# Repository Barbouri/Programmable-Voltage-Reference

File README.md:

# Programmable-Voltage-Reference
An adjustable 0.001 to 5.000 volt reference, adjustable in 1 mV steps with display
==============================

This repository contains the design files and write-up for a Programmable Voltage Reference.  The reference has a range of 1 mV to 5.000 volts in 1 mV steps. The accuracy is plus or minus 50 uV for any set value. The reference value is displayed on a 2 X 16 character OLED display and can be set manually using the rotary encoder or remotely over the TTL serial to isolated USB 2.0 port.

The software folder contains an Arduino / Teensyduino sketch that is the source code for the voltage reference firmware.

Visit https://www.barbouri.com/2022/03/29/updating-the-programmable-voltage-reference-project/ for a more detailed explanation of the project design.

You can order this PCB directly from OSH Park.  Click on the following link.  
  * Programmable Voltage Reference V3.14- https://oshpark.com/shared_projects/pFu2IAUW

See the Bill of Materials (BOM) file in the repo Hardware folder for a parts list.  

## Status  
  * Version 3.14 PCB has been tested to be functional.
  * Version 3.15 PCB is untested with changes to silkscreen values and circuit trace widths.

## File Formats  

Hardware design files are in "CadSoft EAGLE PCB Design Software 7.7" .brd and .sch formats.  A free version of the software can be downloaded from https://www.autodesk.com/products/eagle/free-download.

The example code is in Arduino / Teensyduino .ino format (text).  A free version of the Arduino software can be downloaded from www.arduino.cc.
Teensyduino software add-on for the Arduino IDE can be downloaded from https://www.pjrc.com/teensy/teensyduino.html

Front panel was fabricated by "Front Panel Express" using "Front Panel Designer". A free version of the software can be downloaded from https://www.frontpanelexpress.com/front-panel-designer/download

## Distribution License  

Original design by C. Schnarel 2014 https://github.com/uChip/VoltageReferenceProgrammable

License:
<br /><span xmlns:dct="http://purl.org/dc/terms/" property="dct:title">Programmable Voltage Reference</span> by <a xmlns:cc="http://creativecommons.org/ns#" href="https://github.com/Barbouri/Programmable-Voltage-Reference" property="cc:attributionName" rel="cc:attributionURL">G. Christenson 2022 / C.Schnarel 2014</a> is licensed under a <a rel="license" href="http://creativecommons.org/licenses/by-sa/4.0/">Creative Commons Attribution-ShareAlike 4.0 International License</a>.

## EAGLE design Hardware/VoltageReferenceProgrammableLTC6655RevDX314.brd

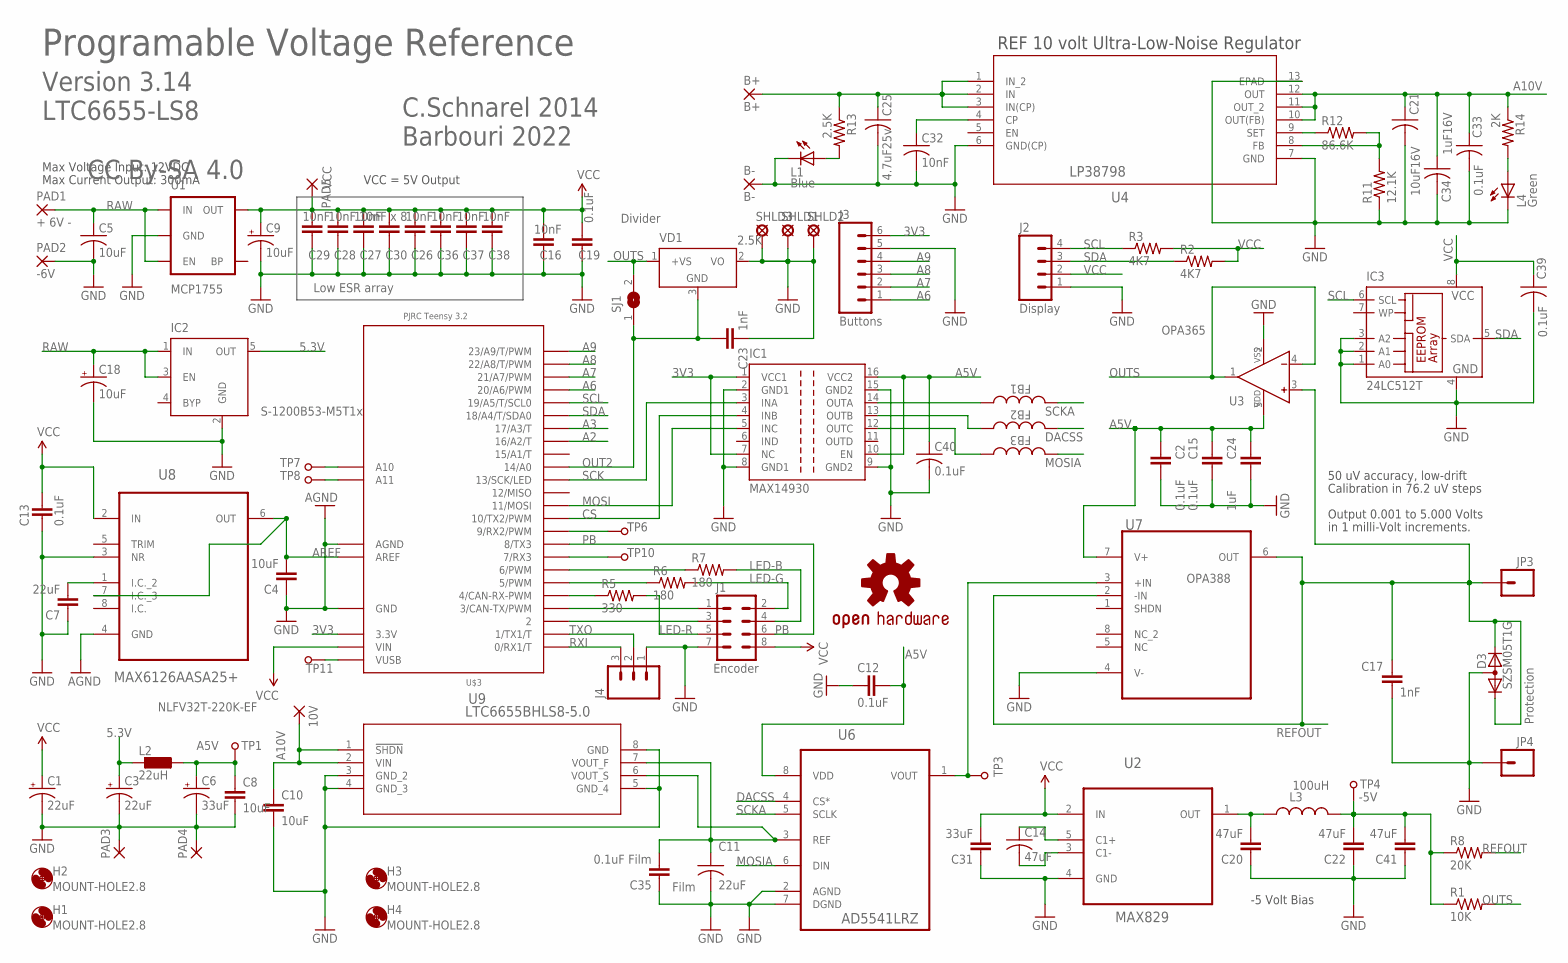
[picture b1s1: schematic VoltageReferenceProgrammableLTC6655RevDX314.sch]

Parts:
10V: 1,6/0,9
B+: B+; 1,6/0,9
B-: B-; 1,6/0,9
C1, C3: 22uF; 0805-POL
C2, C12, C13, C15, C19: 0.1uF; 0805
C4, C8, C10: 10uF; 0805
C5: 10uF; C1206K
C6: 33uF; 0805-POL
C7: 22uF; 0805
C9, C18: 10uF; 0805-POL
C11: 22uF; C2220K
C14: 47uF; C0805
C16, C26, C27, C28, C29, C36, C37, C38: 10nF; C0603K
C17, C23: 1nF; 0805
C20: 47uF; 0805
C21: 10uF16V; C1206
C22, C41: 47uF; 1206
C24: 1uF; 0805
C25: 4.7uF25v; C1206
C30: 10nF x 8; C0603K
C31: 33uF; 0805
C32: 10nF; C0805
C33, C40: 0.1uF; C0603
C34: 1uF16V; C1206
C35: 0.1uF Film; 0805
C39: 0.1uF; C0805
D3: SZSM05T1G; SOT23C
FB1, FB2, FB3: 1K; WE-CBA_0402(W=1.5)
H1, H2, H3, H4: MOUNT-HOLE2.8; 2,8
IC1: MAX14930; SO-16DW
IC2: S-1200B53-M5T1x; SOT23-5
IC3: 24LC512T; SO-08
J1: Encoder; 2X4
J2: Display; 1X04_LOCK
J3: Buttons; 1X06_LOCK
J4: M03LOCK; 1X03_LOCK
JP3, JP4: M01PTH; 1X01
L1: Blue; CHIP-LED0603
L2: 22uH; L3225P
L3: 100uH; 0805
L4: Green; CHIP-LED0603
LOGO1: OSHW-LOGOM; OSHW-LOGO-M
PAD1: + 6V -; 2,15/1,0
PAD2: -6V; 2,15/1,0
PAD3, PAD4, PAD5: 1,6/0,9
R1: 10K; 0805
R2, R3: 4K7; R0603
R5: 330; 0805
R6, R7: 180; 0805
R8: 20K; 0805
R11: 12.1K; 0805
R12: 86.6K; 0805
R13: 2.5K; R0603
R14: 2K; R0603
SHLD1, SHLD3: SHLD1; LSP11
SHLD2: SHLD2; LSP11
SJ1: SJ
TP1, TP3, TP4, TP6, TP7, TP8, TP10, TP11: TEST_POINT; BBD-VIA
U1: MCP1755; SOT23-5
U2: MAX829; SOT95P280X145-5N
U3: OPA365; SOT-23-5
U4: LP38798; DNT12
U6: AD5541LRZ; SOIC127P600X175-8N
U7: OPA388; SOIC127P600X175-8N; MPN OPA388
U8: MAX6126AASA25+; SOIC127P600X175-8N
U9: LTC6655BHLS8-5.0; LCC-8_LS8
U$3: PJRC Teensy 3.2; TEENSY3-DIL+4
VD1: 2.5K; SOT23

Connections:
3V3: IC1.1 (VCC1), IC1.7 (NC), J3.6, U$3.3.3V
5.3V: C3.1 (+), IC2.5 (OUT), L2.2
9: TP6.P$1, U$3.9 (9/RX2/PWM)
-5V: C22.2, C41.2, L3.2, R1.1, R8.1, TP4.P$1
A2: U$3.16/A2 (16/A2/T)
A3: U$3.17/A3 (17/A3/T)
A5V: C2.1, C6.1 (+), C8.1, C12.1, C15.1, C24.1, C40.1, IC1.10 (EN), IC1.16 (VCC2), L2.1, TP1.P$1, U3.5 (VDD), U6.8 (VDD), U7.7 (V+)
A6: J3.1, U$3.20/A6 (20/A6/PWM)
A7: J3.2, U$3.21/A7 (21/A7/PWM)
A8: J3.3, U$3.22/A8 (22/A8/T/PWM)
A9: J3.4, U$3.23/A9 (23/A9/T/PWM)
A10V: 10V.1, C10.1, C21.1, C33.1, C34.1, R14.1, U4.10 (OUT(FB)), U4.11 (OUT_2), U4.12 (OUT), U9.1 (!SHDN), U9.2 (VIN)
AGND: U8.4 (GND)
AREF: C4.2, U8.6 (OUT), U8.7 (I.C._3), U$3.AREF
BATT: B+.1, C25.1, R13.1, U4.1 (IN_2), U4.2 (IN), U4.3 (IN(CP))
CS: IC1.4 (INB), U$3.10 (10/TX2/PWM)
DACSS: FB2.2, U6.4 (CS*)
EA: J1.1, U$3.3 (3/CAN-TX/PWM)
EB: J1.3, U$3.2
GND: B-.1, C1.2 (-), C2.2, C3.2 (-), C4.1, C5.2, C6.2 (-), C7.1, C8.2, C9.2 (-), C10.2, C11.2, C12.2, C13.2, C15.2, C16.1, C17.1, C18.2 (-), C19.1, C20.1, C21.2, C22.1, C23.1, C24.2, C25.2, C26.1, C27.1, C28.1, C29.1, C30.1, C31.1, C32.2, C33.2, C34.2, C35.1, C36.1, C37.1, C38.1, C39.2, C40.2, C41.1, D3.3 (A), IC1.2 (GND1), IC1.8 (GND1), IC1.9 (GND2), IC1.15 (GND2), IC2.2 (GND), IC3.1 (A0), IC3.2 (A1), IC3.3 (A2), IC3.4 (GND), J1.7, J2.1, J3.5, J4.1, JP4.1, L1.C, L4.C, PAD2.1, PAD3.1, PAD4.1, R11.1, SHLD1.MP, SHLD2.MP, SHLD3.MP, U1.2 (GND), U2.4 (GND), U3.2 (VSS), U4.6 (GND(CP)), U4.7 (GND), U4.13 (EPAD), U6.2 (AGND), U6.7 (DGND), U7.4 (V-), U8.3 (NR), U9.3 (GND_2), U9.4 (GND_3), U9.5 (GND_4), U9.8 (GND), U$3.AGND, U$3.GND, VD1.2 (VO)
LED-B: J1.4, R7.2
LED-G: J1.2, R6.2
LED-R: J1.5, R5.2
MOSI: IC1.5 (INC), U$3.11 (11/MOSI)
MOSIA: FB3.2, U6.6 (DIN)
unnamed: R12.1, U4.9 (SET)
unnamed: C7.2, U8.1 (I.C._2)
unnamed: R5.1, U$3.4 (4/CAN-RX-PWM)
unnamed: R6.1, U$3.5 (5/PWM)
unnamed: R7.1, U$3.6 (6/PWM)
unnamed: TP3.P$1, U6.1 (VOUT), U7.3 (+IN)
unnamed: TP7.P$1, U$3.A10
unnamed: C20.2, L3.1, U2.1 (OUT)
unnamed: TP8.P$1, U$3.A11
unnamed: R11.2, R12.2, U4.8 (FB)
unnamed: TP10.P$1, U$3.7 (7/RX3)
unnamed: TP11.P$1, U$3.VUSB
unnamed: C14.2, U2.3 (C1-)
unnamed: C32.1, U4.4 (CP)
unnamed: C14.1, U2.5 (C1+)
unnamed: FB1.1, IC1.14 (OUTA)
unnamed: L1.A, R13.2
unnamed: FB2.1, IC1.13 (OUTB)
unnamed: FB3.1, IC1.12 (OUTC)
unnamed: L4.A, R14.2
OUT2: C23.2, SJ1.1, U$3.14/A0, VD1.3 (GND)
OUTS: R1.2, SJ1.2, U3.1 (OUT), U3.4 (IN-), VD1.1 (+VS)
PB: J1.6, U$3.8 (8/TX3)
RAW: C5.1, C18.1 (+), IC2.1 (IN), IC2.3 (EN), PAD1.1, U1.1 (IN), U1.3 (EN)
REFOUT: C17.2, D3.1 (K1), D3.2 (K2), JP3.1, R8.2, U3.3 (IN+), U7.2 (-IN), U7.6 (OUT)
RXI: J4.3, U$3.0 (0/RX1/T)
SCK: IC1.3 (INA), U$3.13 (13/SCK/LED)
SCKA: FB1.2, U6.5 (SCLK)
SCL: IC3.6 (SCL), J2.4, R3.1, U$3.19/A5 (19/A5/T/SCL0)
SDA: IC3.5 (SDA), J2.3, R2.1, U$3.18/A4 (18/A4/T/SDA0)
TXO: J4.2, U$3.1 (1/TX1/T)
VCC: C1.1 (+), C9.1 (+), C13.1, C16.2, C19.2, C26.2, C27.2, C28.2, C29.2, C30.2, C31.2, C36.2, C37.2, C38.2, C39.1, IC3.8 (VCC), J1.8, J2.2, PAD5.1, R2.2, R3.2, U1.5 (OUT), U2.2 (IN), U8.2 (IN), U$3.VIN
VREF: C11.1, C35.2, U6.3 (REF), U9.6 (VOUT_S), U9.7 (VOUT_F)

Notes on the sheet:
Max Voltage Input: 12VDC
Max Current Output: 300mA
VCC = 5V Output
Programable Voltage Reference
Version 3.14 LTC6655-LS8
Output 0.001 to 5.000 Volts
in 1 milli-Volt increments.
50 uV accuracy, low-drift
Calibration in 76.2 uV steps
C.Schnarel 2014 Barbouri 2022
Protection
Divider
Low ESR array
CC By-SA 4.0
REF 10 volt Ultra-Low-Noise Regulator
-5 Volt Bias

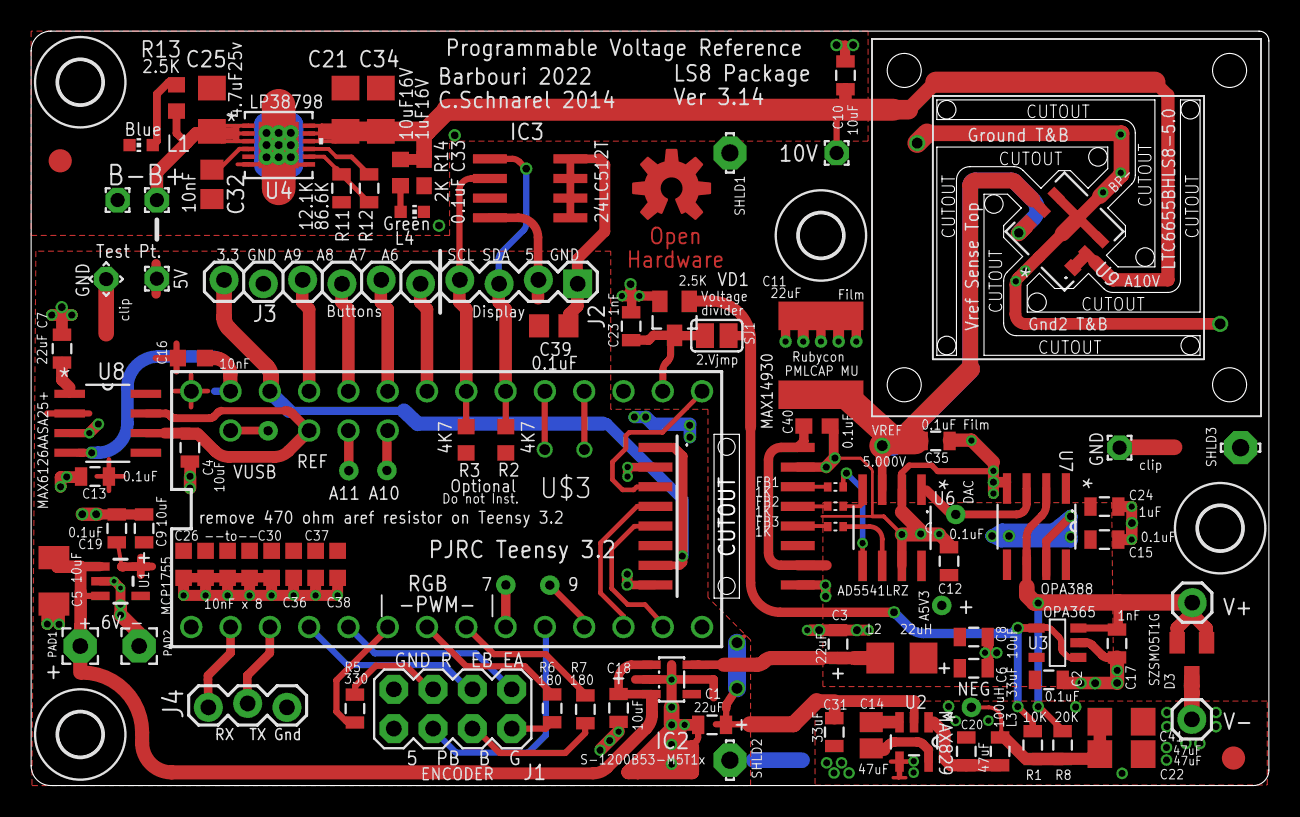
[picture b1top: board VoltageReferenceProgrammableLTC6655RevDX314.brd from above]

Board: 2 copper layers, 80.0 x 48.8 mm, 107 parts (1 on the bottom side), 55 nets.

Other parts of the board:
FID1: 1; FIDUCIAL_G15
FID2: 2; FIDUCIAL_G15
U$1: OSHW-LOGO-M_COPPER

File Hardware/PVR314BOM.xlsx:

Part | Value | Device | Package | Description | MFG | PN
C1 | 22uF | CAP_POL0805 | 0805-POL | Capacitor 22µF Molded Tantalum Polymer 10V 0805 200mOhm | KYOCERA AVX | F381A226MSA
C2 | 0.1uF | CAP0805 | 0805 | Capacitor ceramic bypass
C3 | 22uF | CAP_POL0805 | 0805-POL | Capacitor 22µF Molded Tantalum Polymer 10V 0805 200mOhm | KYOCERA AVX | F381A226MSA
C4 | 10uF | CAP0805 | 0805 | Capacitor
C5 | 10uF | CAP1206 | C1206K | Capacitor 10µF ±10% 16V Ceramic X7R 1206 | Kemet | C1206X105K4RACAUTO
C6 | 33uF | CAP_POL0805 | 0805-POL | Capacitor 33µF Molded Tantalum Polymer 10V 0805 200mOhm | KYOCERA AVX | F381A336MSALZT
C7 | 22uF | CAP0805 | 0805 | Capacitor
C8 | 10uF | CAP0805 | 0805 | Capacitor
C9 | 10uF | CAP_POL0805 | 0805-POL | Capacitor 10µF Molded Tantalum Polymer 10V 0805 200mOhm | KEMET | T529P106M010AAE200
C10 | 10uF | CAP0805 | 0805 | Capacitor
C11 | 22uF | CAP2220 | C2220K | Capacitor Film 22uF 20% 16VDC 2220 | Rubycon | 16MU226MD35750
C12 | 0.1uF | CAP0805 | 0805 | Capacitor ceramic bypass
C13 | 0.1uF | CAP0805 | 0805 | Capacitor ceramic bypass
C14 | 47uF | CAP0805 | C0805 | Capacitor 47µF ±20% 10V Ceramic X5R 0805 | KYOCERA AVX | 0805ZD476MAT2A
C15 | 0.1uF | CAP0805 | 0805 | Capacitor ceramic bypass
C16 | 10nF | CAP0603 | C0603K | Capacitor ceramic bypass
C17 | 1nF | CAP0805 | 0805 | Capacitor ceramic bypass C0G
C18 | 10uF | CAP_POL0805 | 0805-POL | Capacitor 10µF Molded Tantalum Polymer 10V 0805 200mOhm | KEMET | T529P106M010AAE200
C19 | 0.1uF | CAP0805 | 0805 | Capacitor ceramic bypass
C20 | 47uF | CAP0805 | 0805 | Capacitor
C21 | 10uF16V | CAP1206 | C1206 | Capacitor 10 µF ±10% 16V Ceramic X7R 1206 | Kemet | C1206X106K4RACAUTO
C22 | 47uF | CAPPOL1206 | 1206 | Capacitor Tantalum Polymer 6.3 V 1206 45mOhm | Vishay Spraque | T55A107M6R3C0045
C23 | 1nF | CAP0805 | 0805 | Capacitor
C24 | 1uF | CAP0805 | 0805 | Capacitor
C25 | 4.7uF25v | CAP1206 | C1206 | Capacitor
C26 | 10nF | CAP0603 | C0603K | Capacitor ceramic bypass
C27 | 10nF | CAP0603 | C0603K | Capacitor ceramic bypass
C28 | 10nF | CAP0603 | C0603K | Capacitor ceramic bypass
C29 | 10nF | CAP0603 | C0603K | Capacitor ceramic bypass
C30 | 10nF x 8 | CAP0603 | C0603K | Capacitor ceramic bypass
C31 | 33uF | CAP0805 | 0805 | Capacitor 33 µF Molded Tantalum Polymer 10V 0805 200mOhm | KYOCERA AVX | F381A336MSALZT
C32 | 10nF | CAP0805 | C0805 | Capacitor ceramic bypass
C33 | 0.1uF | CAP0603 | C0603 | Capacitor ceramic bypass
C34 | 1uF16V | CAP1206 | C1206 | Capacitor 1 µF ±10% 16V Ceramic X7R 1206 | Kemet | C1206X105K4RACAUTO
C35 | 0.1uF Film | CAP0805 | 0805 | Capacitor Film 0.1uF 20% 16VDC 2220 | Rubycon | 25MU104KZ22012
C36 | 10nF | CAP0603 | C0603K | Capacitor ceramic bypass
C37 | 10nF | CAP0603 | C0603K | Capacitor ceramic bypass
C38 | 10nF | CAP0603 | C0603K | Capacitor ceramic bypass
C39 | 0.1uF | CAP0805 | C0805 | Capacitor ceramic bypass
C40 | 0.1uF | CAP0603 | C0603 | Capacitor ceramic bypass
C41 | 47uF | CAPPOL1206 | 1206 | Capacitor Tantalum Polymer 6.3 V 1206 45mOhm | Vishay Spraque | T55A107M6R3C0045
D3 | SZSM05T1G | DIODE_CA-AC__ | SOT23C | 5V RS 9.8V Clamp 17A Ipp Tvs Diode Surface Mount SOT-23-3 | On Semiconductor | SZSM05T1G
FB1 | 1K | Ferrite Bead Inductor | 0402 | Ferrite Bead Inductor 1 kOhms @ 100 MHz SMD 0402 | Murata | BLM15HG102SH1D
FB2 | 1K | Ferrite Bead Inductor | 0402 | Ferrite Bead Inductor 1 kOhms @ 100 MHz SMD 0402 | Murata | BLM15HG102SH1D
FB3 | 1K | Ferrite Bead Inductor | 0402 | Ferrite Bead Inductor 1 kOhms @ 100 MHz SMD 0402 | Murata | BLM15HG102SH1D
IC1 | MAX14930 | ISO7240 | SO-16DW | Digital Isolator 2750Vrms 4 Channel 25Mbps 16-SOIC-Wide | Analog Devices Inc./Maxim | MAX14930EAWE+
IC2 | S-1200B53-M5T1x | MIC5219XX | SOT23-5 | IC REG LINEAR 5.3V 150MA SOT23-5 | ABLIC Inc. | S-1200B53-M5T1U
IC3 | 24LC64SN | SO8-EEPROM | SO-08 | Serial EEPROM 64/128/256/or 512K | MICROCHIP | 24LC64-I/SN
J1 | Encoder | M04X2 | 2X4 | 0.1" spacing Header, two rows of four | TE Connectivity AMP Connectors | 826656-4
J2 | Display | M04X1 | 1X04_LOCK | 0.1" spacing Header 4 part of 1X16 piece | TE Connectivity AMP Connectors | 1-825433-6
J3 | Buttons | M06X1 | 1X06_LOCK | 0.1" spacing Header 6 part of 1X16 piece | TE Connectivity AMP Connectors
J4 | Serial | M03X1 | 1X03_LOCK | 0.1" spacing Header 3 part of 1X16 piece | TE Connectivity AMP Connectors
H1T | Teensy-R | M14X1 | 1X14 | Connector Header Through Hole 14 position 0.100" series 350 | Mill-Max Manufacturing Corp. | 350-10-114-00-006000
H1B | Teensy-R | F14X1 | 1X14 | Connector Header Through Hole 14 position 0.100" series 350 | Mill-Max Manufacturing Corp. | 310-41-114-41-001000
H2T | Teensy-L | M14X1 | 1X14 | Connector Header Through Hole 14 position 0.100" series 350 | Mill-Max Manufacturing Corp. | 350-10-114-00-006000
H2B | Teensy-L | F14X1 | 1X14 | Connector Header Through Hole 14 position 0.100" series 350 | Mill-Max Manufacturing Corp. | 310-41-114-41-001000
H3T | Teensy-I | M05X1 | 1X5 -1 | Connector Header Through Hole 5 position 0.100" Remove 1 pos | Mill-Max Manufacturing Corp. | 350-10-105-00-006000
H3B | Teensy-I | F05X1 | 1X5 -1 | Connector Header Through Hole 5 position 0.100" Remove 1 pos | Mill-Max Manufacturing Corp. | 310-41-105-41-001000
L1 | Blue | 0603-LED | 0603 | LED Blue 0603 | Kingbright | APHM1608VRBXF/A-5
L2 | 22uH | 1210-IND | 1210 | INDUCTOR 22µH Shielded Wirewound 120mA 480mOhm Max | TDK Corporation | NLFV32T-220K-EF
L3 | 100uH | 0805-IND | 0805 | Inductors 100UH 50MA 4 OHM SMD | Taiyo Yuden | LBR2012T101KV
L4 | Green | 0603-LED | 0603 | LED Green 0603 | Vishay Semiconductor | VLMTG1300-GS08
R1 | 10K | 0805-RES | 0805 | Resistor 1% to 5%
R2 | 4.7K | 0603-RES | 0603 | Resistor Optional for testing - Do Not Install
R3 | 4.7K | 0603-RES | 0603 | Resistor Optional for testing - Do Not Install
R5 | 330 | 0805-RES | 0805 | Resistor 1% to 5%
R6 | 180 | 0805-RES | 0805 | Resistor 1% to 5%
R7 | 180 | 0805-RES | 0805 | Resistor 1% to 5%
R8 | 20K | 0805-RES | 0805 | Resistor 1% to 5%
R11 | 12.1K | 0805-RES | 0805 | Resistor ±0.1% 0.125W, 1/8W | Vishay Dale | TNPW080512K1BEEA
R12 | 86.6K | 0805-RES | 0805 | Resistor ±0.1% 0.125W, 1/8W | Vishay Dale | TNPW080580K6BEEN
R13 | 2.5K | 0603-RES | 0603 | Resistor 1% to 5%
R14 | 2K | 0603-RES | 0603 | Resistor 1% to 5%
U$3 | PJRC Teensy 3.2 | TEENSY_3.1_DIL+4 | TEENSY-DIL+4 | Teensy 3.1 and 3.2 in a DIL package with the inner 4 pins
U1 | MCP1755 | V_REG_LDOSMD | SOT-23-5 | IC REG LINEAR 5V 300MA SOT23-5 LDO | Microchip Technology | MCP1755T-5002E/OT
U2 | MAX829 | MAX829EUK+T | SOT-23-5 | Switched-Capacitor Voltage Inverters | Maxim | MAX829EUK+T
U3 | OPA365 | OPA365 | SOT-23-5 | General Purpose Amplifier 1 Circuit Rail-to-Rail SOT-23-5 | Texas Instruments | OPA365AIDBVR
U4 | LP38798 | LP38798SD-ADJ | DNT12 |  | Texas Instruments | LP38798SD-ADJ/NOPB
U6 | AD5541LRZ | AD5541LRZ | SOIC-8 | 16-Bit Digital-to-Analog Converters | Analog Devices | AD5541LRZ
U7 | OPA388 | LTC2050IS8PBF | SOIC-8 | Zero-Drift Operational Amplifi ers | Linear Technology | OPA388
U8 | MAX6126AASA25+ | Voltage Reference | SOIC-8 | Series, Buried Zener Reference. Fixed 2.5V 0.04% 15mA 8-SOIC | Analog Devices Inc./Maxim | MAX6225ACSA+
U9 | LTC6655BHLS8-5.0 | Voltage Reference | LCC-8_LS8 | Series Voltage Ref. IC Fixed 5V 0.025% 5 mA 8-CLCC | Linear Technology | LTC6655BHLS8-5.000
VD1 | 2.5K-2.5K | LM50 | SOT-23 | SOT-23 Voltage Divider

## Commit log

2022-03-27 Add files via upload
    Teensyduino sketch for the Programmable Voltage Reference (PVR) hardware version 3.14 and 3,18
2022-03-28 Update VoltageReferenceProgrammableTeensyOLEDrev300.ino
    Notes and Version update
2022-03-30 Create Hardware
2023-02-09 Update VoltageReferenceProgrammableTeensyOLEDrev300.ino
    Changed MAXVAL and MINVAL from uint32_t to int16_t integers to correct:
    warning: comparison between signed and unsigned integer expressions [-Wsign-compare]
    if (refVal > MAXVAL) refVal = 1;
2023-02-12 Add Revision 3.00 documentation PDF

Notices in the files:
parts and their libraries:
SparkFun-Resistors: Licensing: Creative Commons ShareAlike 4.0 International - https://creativecommons.org/licenses/by-sa/4.0
SparkFun-Capacitors: Licensing: CC v3.0 Share-Alike You are welcome to use this library for commercial purposes.
EMCComponents: Copyright: Würth Elektronik
